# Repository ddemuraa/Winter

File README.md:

# Winter
2-key Hall effect keypad made for osu! with rapid trigger, dedicated for aespa's member "WINTER" with their newest track "I'm Unhappy"

Designed in KiCad 7.0.2

# Features
- Uses [minipad firmware](https://github.com/minipadKB/minipad-firmware)
- Powered using RP2040 with 128MB of flash memory
- Uses SK6812MINI-E for per-key RGBs
- Rapid Trigger with adjustable actuation

# Case
- STL file for 3D print is available in `3D Case file`
- Designed in Fusion 360
- Made into 2 parts
- 2cm tall

# Assembly 
All assembly files for JLCPCB manufacture are available in `Gerber, BOM & CPL`

# WIP
- add photos of pcb IRL

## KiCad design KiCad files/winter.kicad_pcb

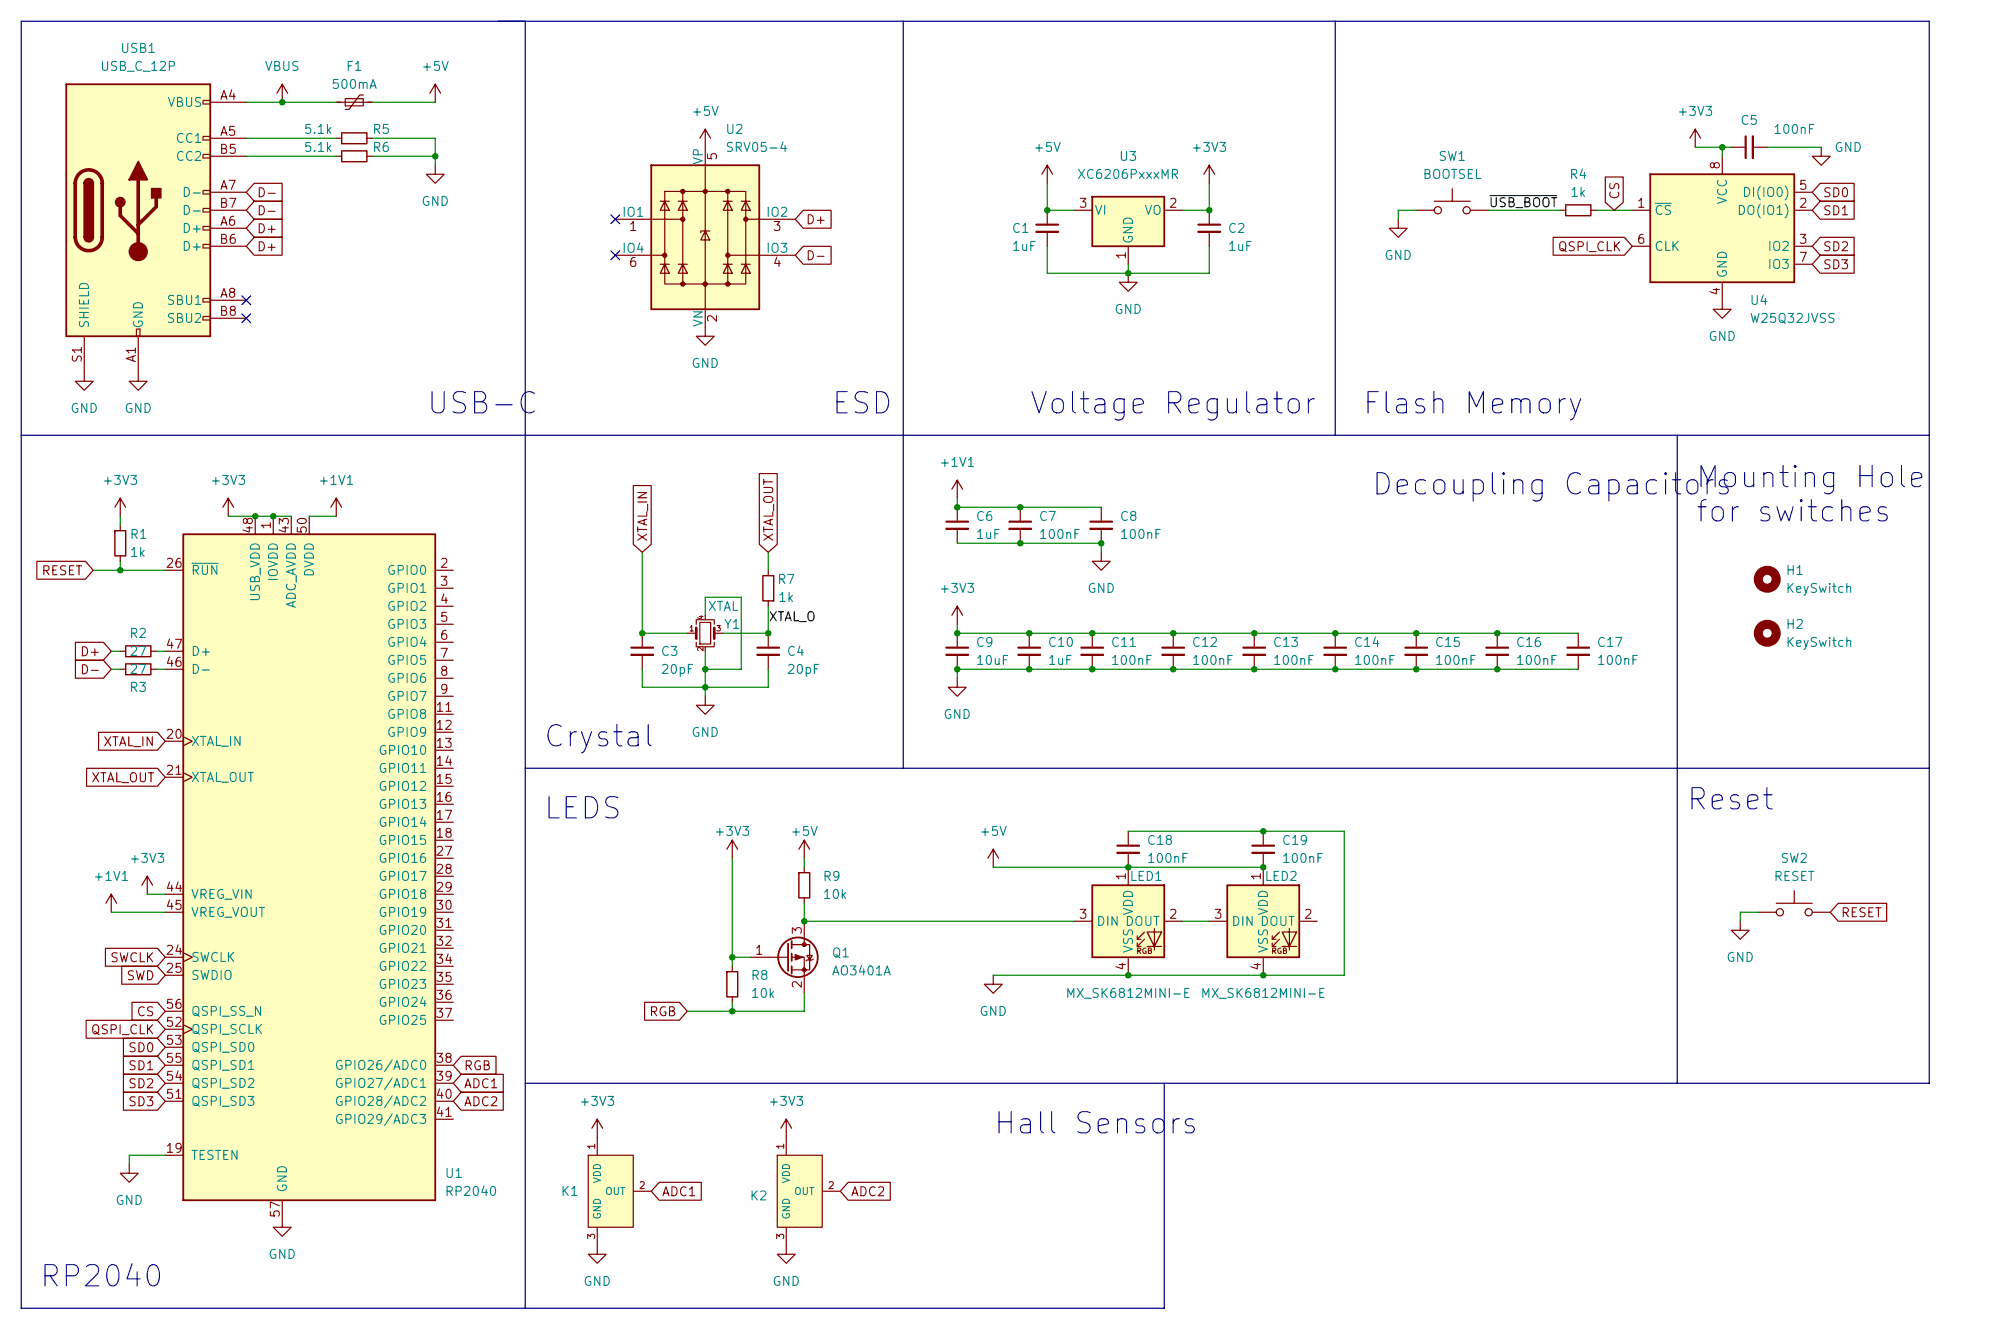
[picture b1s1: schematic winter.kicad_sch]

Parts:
C1, C2, C6, C10: 1uF; C_0402_1005Metric
C3, C4: 20pF; C_0402_1005Metric
C5, C7, C8, C11, C12, C13, C14, C15, C16, C17, C18, C19: 100nF; C_0402_1005Metric
C9: 10uF; C_0402_1005Metric
F1: 500mA; Fuse_0805_2012Metric
H1, H2: KeySwitch; MXOnly-1U-FLIPPED
K1, K2: Hall_Sensor; SOT-23; MPN GH39FKSW; LCSC Part C266230
LED1, LED2: MX_SK6812MINI-E; LED_MX_6028R-ROT
Q1: AO3401A; SOT-23
R1, R4, R7: 1k; R_0402_1005Metric
R2, R3: 27; R_0603_1608Metric
R5, R6: 5.1k; R_0402_1005Metric
R8, R9: 10k; R_0402_1005Metric
SW1: BOOTSEL; SolderJumper-2_P1.3mm_Bridged_Pad1.0x1.5mm
SW2: RESET; SolderJumper-2_P1.3mm_Bridged_Pad1.0x1.5mm
U1: RP2040; RP2040-QFN-56
U2: SRV05-4; SOT-23-6-routable
U3: XC6206PxxxMR; SOT-23
U4: W25Q32JVSS; SOIC-8_5.23x5.23mm_P1.27mm
USB1: USB_C_12P; USB_C_Receptacle_HRO_TYPE-C-31-M-12
Y1: XTAL; Crystal_SMD_3225-4Pin_3.2x2.5mm

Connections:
+1V1: C6.1, C7.1, C8.1, U1.23 (DVDD), U1.45 (VREG_VOUT), U1.50 (DVDD)
+3V3: C2.1, C5.1, C9.1, C10.1, C11.1, C12.1, C13.1, C14.1, C15.1, C16.1, C17.1, K1.1 (VDD), K2.1 (VDD), Q1.1 (G), R1.1, R8.1, U1.1 (IOVDD), U1.10 (IOVDD), U1.22 (IOVDD), U1.33 (IOVDD), U1.42 (IOVDD), U1.43 (ADC_AVDD), U1.44 (VREG_VIN), U1.48 (USB_VDD), U1.49 (IOVDD), U3.2 (VO), U4.8 (VCC)
+5V: C1.1, C18.2, C19.2, F1.2, LED1.1 (VDD), LED2.1 (VDD), R9.1, U2.5 (VP), U3.3 (VI)
/XTAL_O: C4.1, R7.1, Y1.3
/~USB_BOOT: R4.1, SW1.2
ADC1: K1.2 (OUT), U1.39 (GPIO27/ADC1)
ADC2: K2.2 (OUT), U1.40 (GPIO28/ADC2)
CS: R4.2, U1.56 (QSPI_SS_N), U4.1 (~CS)
D+: R2.1, U2.3 (IO2), USB1.A6 (D+), USB1.B6 (D+)
D-: R3.1, U2.4 (IO3), USB1.A7 (D-), USB1.B7 (D-)
GND: C1.2, C2.2, C3.2, C4.2, C5.2, C6.2, C7.2, C8.2, C9.2, C10.2, C11.2, C12.2, C13.2, C14.2, C15.2, C16.2, C17.2, C18.1, C19.1, K1.3 (GND), K2.3 (GND), LED1.4 (VSS), LED2.4 (VSS), R5.2, R6.2, SW1.1, SW2.1, U1.19 (TESTEN), U1.57 (GND), U2.2 (VN), U3.1 (GND), U4.4 (GND), USB1.A1 (GND), USB1.A12 (GND), USB1.B1 (GND), USB1.B12 (GND), USB1.S1 (SHIELD), Y1.2, Y1.4
unnamed: LED1.3 (DIN), Q1.3 (D), R9.2
unnamed: LED1.2 (DOUT), LED2.3 (DIN)
unnamed: R2.2, U1.47 (D+)
unnamed: R3.2, U1.46 (D-)
unnamed: R5.1, USB1.A5 (CC1)
unnamed: R6.1, USB1.B5 (CC2)
QSPI_CLK: U1.52 (QSPI_SCLK), U4.6 (CLK)
RESET: R1.2, SW2.2, U1.26 (~RUN)
RGB: Q1.2 (S), R8.2, U1.38 (GPIO26/ADC0)
SD0: U1.53 (QSPI_SD0), U4.5 (DI(IO0))
SD1: U1.55 (QSPI_SD1), U4.2 (DO(IO1))
SD2: U1.54 (QSPI_SD2), U4.3 (IO2)
SD3: U1.51 (QSPI_SD3), U4.7 (IO3)
SWCLK: U1.24 (SWCLK)
SWD: U1.25 (SWDIO)
VBUS: F1.1, USB1.A4 (VBUS), USB1.A9 (VBUS), USB1.B4 (VBUS), USB1.B9 (VBUS)
XTAL_IN: C3.1, U1.20 (XTAL_IN), Y1.1
XTAL_OUT: R7.2, U1.21 (XTAL_OUT)

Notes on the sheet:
LEDS
ESD
Hall Sensors
USB-C
Mounting Hole for switches
Decoupling Capacitors
Flash Memory
RP2040
Crystal
Voltage Regulator
Reset

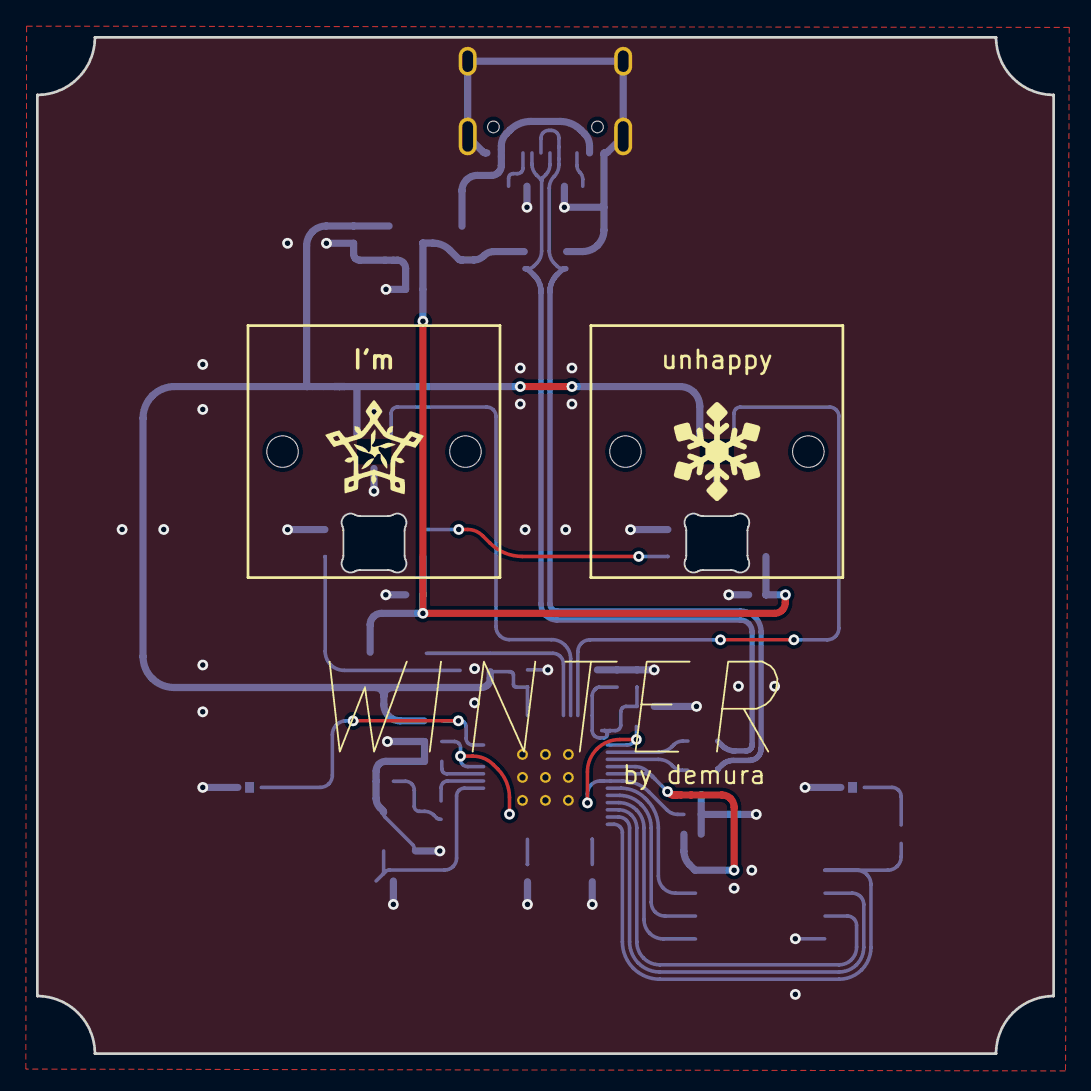
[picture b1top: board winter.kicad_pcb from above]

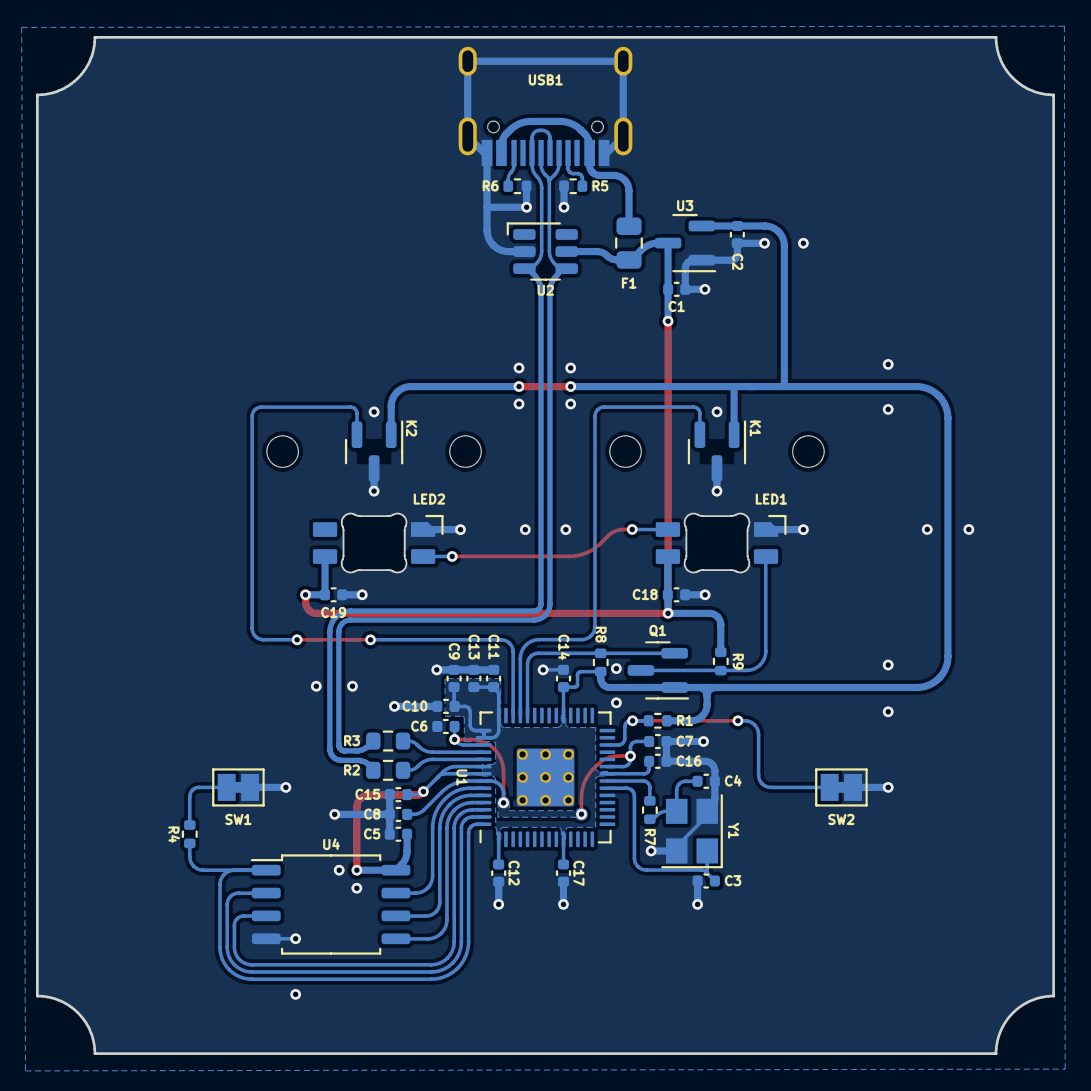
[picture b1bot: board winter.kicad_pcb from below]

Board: 2 copper layers, 56.5 x 56.5 mm, 44 parts (44 on the bottom side), 27 nets.

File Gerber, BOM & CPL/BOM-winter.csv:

Comment,Designator,Footprint,LCSC
1k,"R1,R4,R7",R_0402_1005Metric,C11702
AO3401A,Q1,SOT-23,C15127
100nF,"C11,C12,C13,C14,C15,C16,C17,C18,C19,C5,C7,C8",C_0402_1005Metric,C1525
10uF,C9,C_0402_1005Metric,C15525
20pF,"C3,C4",C_0402_1005Metric,C1554
USB_C_12P,USB1,USB_C_Receptacle_HRO_TYPE-C-31-M-12,C165948
RP2040,U1,RP2040-QFN-56,C2040
10k,"R8,R9",R_0402_1005Metric,C25086
27,"R2,R3",R_0603_1608Metric,C25190
5.1k,"R5,R6",R_0402_1005Metric,C25905
Hall_Sensor,"K1,K2",SOT-23,C2904393
MX_SK6812MINI-E,"LED1,LED2",LED_MX_6028R-ROT,C5149201
1uF,"C1,C10,C2,C6",C_0402_1005Metric,C52923
SRV05-4,U2,SOT-23-6-routable,C85364
500mA,F1,Fuse_0805_2012Metric,C883105
W25Q32JVSS,U4,SOIC-8_5.23x5.23mm_P1.27mm,C97521
XTAL,Y1,Crystal_SMD_3225-4Pin_3.2x2.5mm,
XC6206PxxxMR,U3,SOT-23,
